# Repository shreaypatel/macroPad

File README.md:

This repository contains the relevant documentation for my custom macropad project. I designed this macropad to be slim, portable and minimalist to match my use case needs. I will primarily use it for onshape CAD shortcuts, 
but I am looking to explore setting up a different mode on it for KiCad shortcuts. The macropad connects to a computer via usb c. I began my design process with the wiring of the schematic. Here I opted for a 3x2 keyboard matrix 
to set up the switch connections. This takes up less input connections on the microcontroller while allowing me to customize 6 individual cherry mx switches. Next, I connected the diodes in between the switches to prevent keyboard
ghosting. Lastly, I set up a rotary rotary encoder switch for the zoom function on onshape CAD. This is the **CAD onshape source file (https://cad.onshape.com/documents/c0725aa56d0443495cbb7afd/w/927aa1fb6a4206026ca4e494/e/48b73c10d6aff836ede0c6ac?renderMode=0&uiState=699fbaea2beaf6245266bbff)**

With the schematic complete I moved onto routing the connections on the actual pcb. I also 
organized the layout of the pcb at this stage and ensured that all connections were wired up properly. 

With the elctrical side of things completed I moved onto desiging the 3D printed enclosure for the macropad. Here I built a minimalistic case with cutouts for the switches and rotary encoder switch. I also created a cutout for the USB C connection
port. Notably, I decided to forgo using screws to secure the top and bottom parts of the enclosure. Instead I opted for a press fit conneciton with 4 3D printed studs that connect directly to the top part of the case. These slot into a square shaped
hole in the bottom of the case. This makes the prototyping process easier and allows me to qucikly clean the internals of the macropad if need be. I applied a chamfer to the 4 studs to ensure they smoothly slot into the bottom of the case. I also included 
an elevated platform support for the pcb to rest on in the enclosure. Superglue can also be used to more securely attach the pins into their respective holes. 

This concludes my design process. Overall, I had a lot of fun making this project and I would say my favourite part was learning how to use KiCad to design PCBs for the first time. 

**BOM:**

* 1 x 3D printed case
* 1 x SEEED XIAO RP2040
* 4 x CHERRY MX keyswitches
* 1 x EC11 rotary encoder
* 6 x 1N4148 diodes

Final Image of CAD and electronics together:

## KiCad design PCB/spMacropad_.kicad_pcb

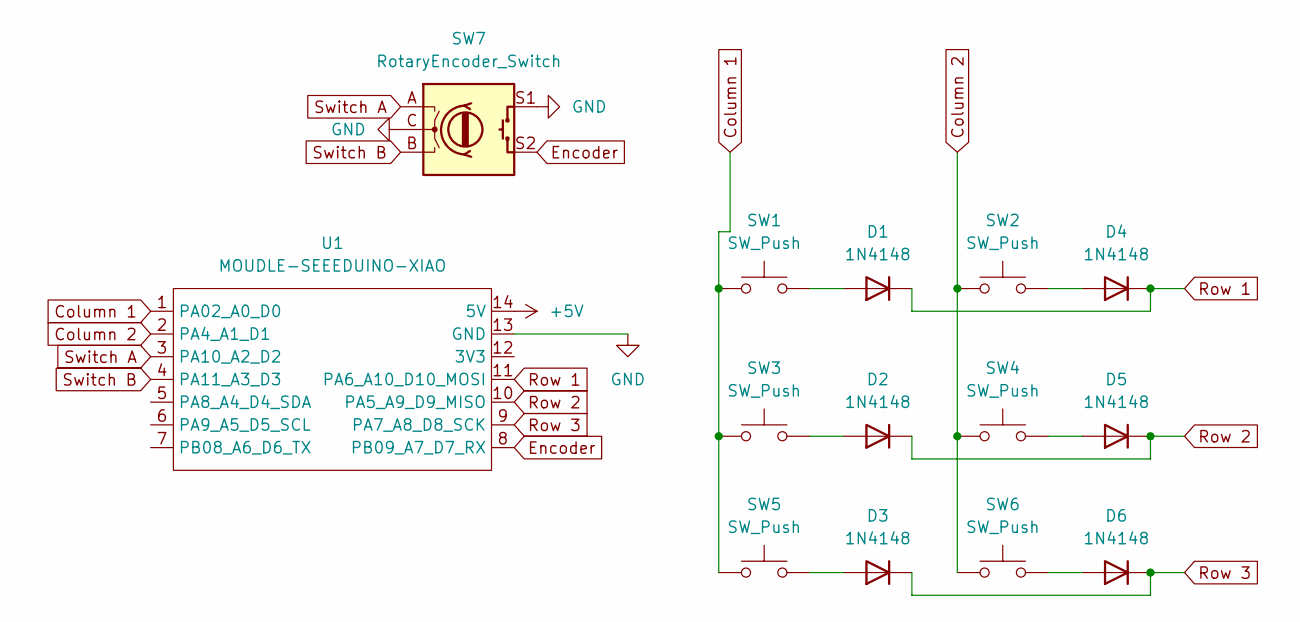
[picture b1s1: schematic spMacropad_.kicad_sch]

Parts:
D1, D2, D3, D4, D5, D6: 1N4148; D_DO-35_SOD27_P7.62mm_Horizontal
SW1, SW2, SW3, SW4, SW5, SW6: SW_Push; SW_Cherry_MX_1.00u_PCB
SW7: RotaryEncoder_Switch; RotaryEncoder_Alps_EC11E-Switch_Vertical_H20mm
U1: MOUDLE-SEEEDUINO-XIAO; XIAO-Generic-Hybrid-14P-2.54-21X17.8MM

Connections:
+5V: U1.14 (5V)
Column 1: SW1.1, SW3.1, SW5.1, U1.1 (PA02_A0_D0)
Column 2: SW2.1, SW4.1, SW6.1, U1.2 (PA4_A1_D1)
Encoder: SW7.S2, U1.8 (PB09_A7_D7_RX)
GND: SW7.C, SW7.S1, U1.13 (GND)
I2C A: U1.5 (PA8_A4_D4_SDA)
I2C B: U1.6 (PA9_A5_D5_SCL)
unnamed: D1.2 (A), SW1.2
unnamed: D2.2 (A), SW3.2
unnamed: D3.2 (A), SW5.2
unnamed: D4.2 (A), SW2.2
unnamed: D5.2 (A), SW4.2
unnamed: D6.2 (A), SW6.2
Row 1: D1.1 (K), D4.1 (K), U1.11 (PA6_A10_D10_MOSI)
Row 2: D2.1 (K), D5.1 (K), U1.10 (PA5_A9_D9_MISO)
Row 3: D3.1 (K), D6.1 (K), U1.9 (PA7_A8_D8_SCK)
Switch A: SW7.A, U1.3 (PA10_A2_D2)
Switch B: SW7.B, U1.4 (PA11_A3_D3)

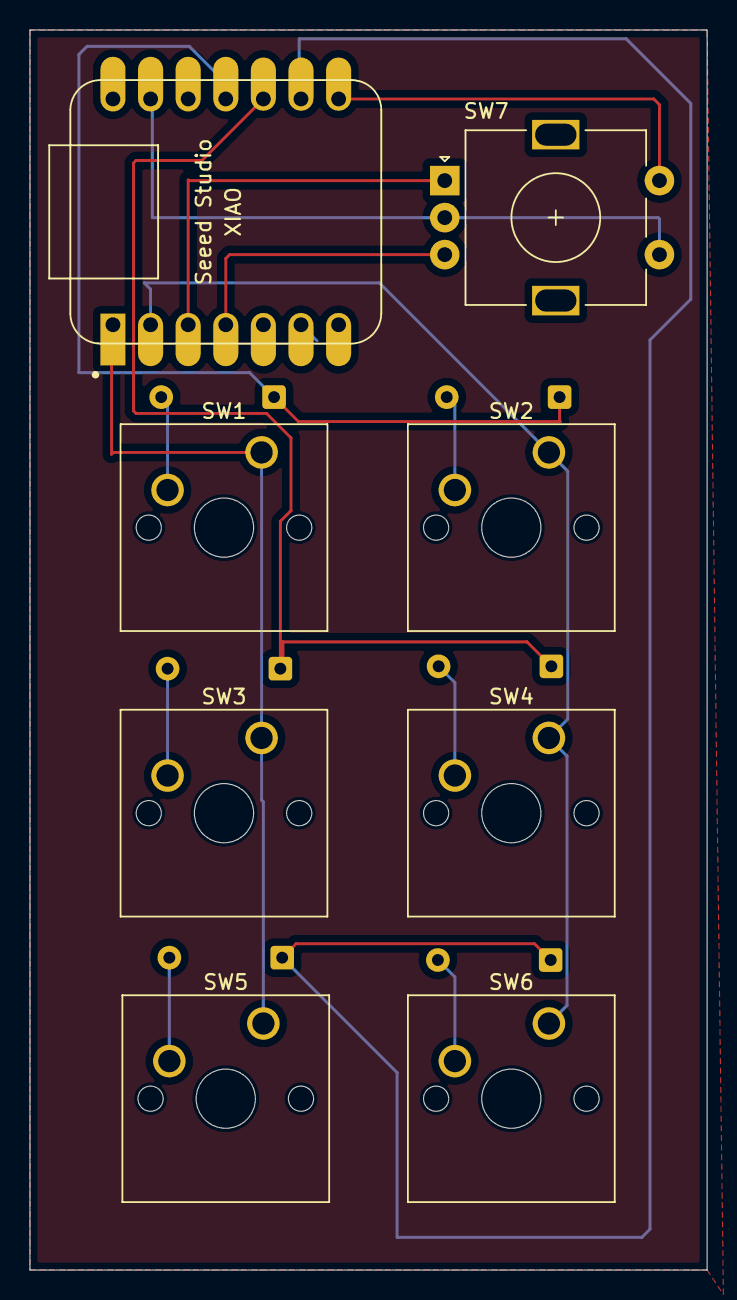
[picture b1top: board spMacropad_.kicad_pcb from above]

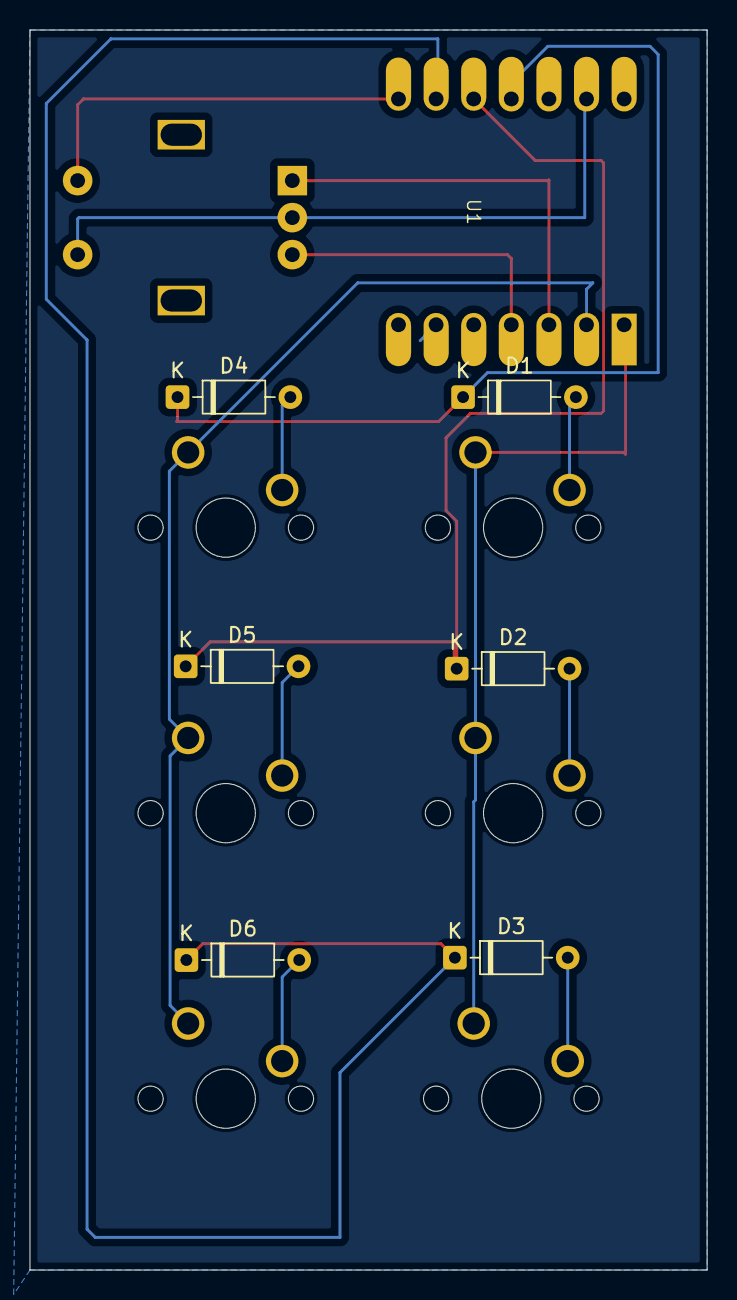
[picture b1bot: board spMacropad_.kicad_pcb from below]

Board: 2 copper layers, 45.7 x 83.8 mm, 14 parts (6 on the bottom side), 15 nets.

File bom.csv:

Designator,Footprint,Quantity,Value,LCSC Part #
"D1, D2, D3, D4, D5, D6",D_DO-35_SOD27_P7.62mm_Horizontal,6,1N4148,
"SW1, SW2, SW3, SW4, SW5, SW6",SW_Cherry_MX_1.00u_PCB,6,SW_Push,
SW7,RotaryEncoder_Alps_EC11E-Switch_Vertical_H20mm,1,RotaryEncoder_Switch,
U1,XIAO-Generic-Hybrid-14P-2.54-21X17.8MM,1,MOUDLE-SEEEDUINO-XIAO,

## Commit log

2026-02-19 Create CAD
2026-02-19 Create text
